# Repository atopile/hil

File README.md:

# Hardware Test 🧪 for Happy Engineers, PMs and CTOs

Hardware-in-the-Loop, or HiL (sometimes HitL), is a way to continuously validate your hardware and firmware together. By connecting actual hardware to virtual test scenarios, HiL enables thorough testing of embedded systems, control units, and firmware under realistic conditions without the risks and costs of full physical testing.

HiL testing catches integration issues early, accelerates development cycles, and ensures robust system performance before deployment. Typically the domain of the most sophisticated automotive and aerospace companies, this HiL suite is now for all 🚀.

## Usage

If you haven't already, get [atopile](https://docs.atopile.io/dev/quickstart/) and run through the quickstart and tutorial.

This suite is intended to be used as a dependency on your project. So, create a new project (`ato create project`) and add this suite as a dependency (`ato install https://github.com/atopile/hil`)

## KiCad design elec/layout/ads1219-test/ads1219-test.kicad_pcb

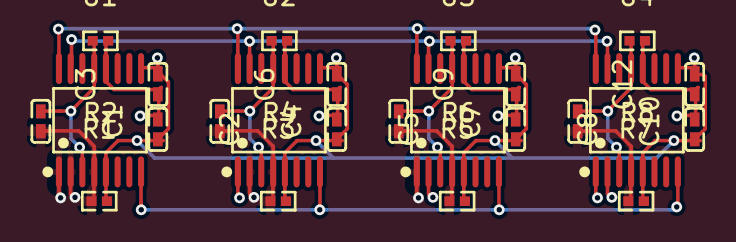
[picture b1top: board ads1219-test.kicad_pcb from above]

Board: 2 copper layers, 24 parts (0 on the bottom side), 14 nets.

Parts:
C1, C2, C3, C4, C5, C6, C7, C8, C9, C10, C11, C12: 1µF ±10% 25V X5R; C0402-b3ef17
R1, R2, R3, R4, R5, R6, R7, R8: 0Ω 62.5mW; R0402-56259e
U1, U2, U3, U4: TSSOP-16_L5.0-W4.4-P0.65-LS6.4-BL-4f6acc

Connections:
REFN: U1.8, U2.8, U3.8, U4.8
SCL: U1.16, U2.16, U3.16, U4.16
SDA: U1.15, U2.15, U3.15, U4.15
adcs[0]-AVDD: C2.1, C3.1, R2.1, U1.12
adcs[0]-gnd: C2.2, C3.2, R1.2, U1.5
adcs[1]-AVDD: C5.1, C6.1, R4.1, U2.12
adcs[1]-gnd: C5.2, C6.2, R3.2, U2.5
adcs[2]-AVDD: C8.1, C9.1, R6.1, U3.12
adcs[2]-gnd: C8.2, C9.2, R5.2, U3.5
adcs[3]-AVDD: C11.1, C12.1, R8.1, U4.12
adcs[3]-gnd: C11.2, C12.2, R7.2, U4.5
gnd: U1.9, U2.9, U3.9, U4.9
gnd-1: C1.2, C4.2, C7.2, C10.2, R1.1, R3.1, R5.1, R7.1, U1.1, U1.2, U1.4, U2.2, U2.4, U3.1, U3.4, U4.4
hv: C1.1, C4.1, C7.1, C10.1, R2.2, R4.2, R6.2, R8.2, U1.3, U1.13, U2.1, U2.3, U2.13, U3.2, U3.3, U3.13, U4.1, U4.2, U4.3, U4.13

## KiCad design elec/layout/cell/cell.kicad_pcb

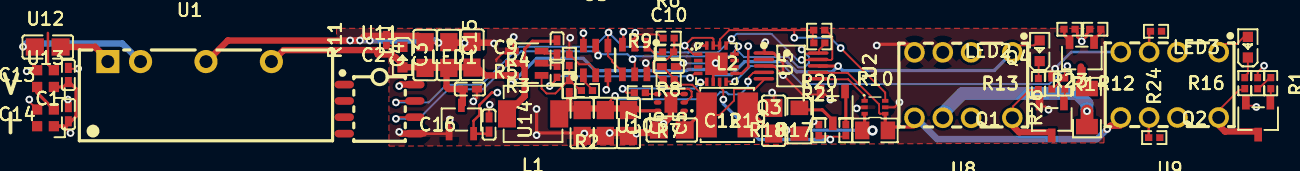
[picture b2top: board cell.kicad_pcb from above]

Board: 4 copper layers, 64 parts (0 on the bottom side), 43 nets.

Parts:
C1: 2.2µF ±10% 25V X7R; C0805-3b2e55
C2, C3, C4, C5, C6, C7, C11, C12: 10µF ±10% 25V X5R; C0805-3b2e55
C9, C13, C14: 100nF ±10% 16V X7R; C0402-b3ef17
C10, C15, C16: 1µF ±10% 25V X5R; C0402-b3ef17
L1: IND-SMD_L4.4-W4.2-3ea78a
L2: IND-SMD_L4.0-W4.0-81e2fd
LED1, LED2, LED3: LED0603-RD-c81ffb
Q1, Q2, Q3, Q4: SOT-23-3_L2.9-W1.6-P1.90-LS2.8-BR-186170
R1, R11, R14: 2kΩ ±1% 62.5mW; R0402-56259e
R2: 24kΩ ±1% 62.5mW; R0402-56259e
R3: 37.4kΩ ±1% 62.5mW; R0402-56259e
R4, R5, R8, R9, R12, R15, R18, R20, R21, R23, R24, R25: 10kΩ ±1% 62.5mW; R0402-56259e
R6: 43kΩ ±1% 62.5mW; R0402-56259e
R7: 60.4kΩ ±1% 62.5mW; R0402-56259e
R10: 100mΩ ±1% 125mW; R0805-c79e8b
R13, R16, R17, R22: 1kΩ ±1% 62.5mW; R0402-56259e
R19: 100Ω ±1% 125mW; R0805-c79e8b
R26: 100Ω ±1% 250mW; R1206-bdb864
U1: PWRM-TH_BXXXXS-2WR3-d8b2fb
U2: MSOP-10_L3.0-W3.0-P0.50-LS5.0-BL-752175
U3, U4, U10: SOT-23-6_L2.9-W1.6-P0.95-LS2.8-BL
U5: QFN-16_L3.0-W3.0-P0.50-BL-EP1.7-3a4c56
U6: WSON-6_L2.0-W2.0-P0.65-TL-EP
U7: SOT-563_L1.6-W1.2-P0.50-LS1.6-TL
U8, U9: RELAY-TH_HFDXXX-689a1e
U11: SOIC-8_L4.9-W3.9-P1.27-LS6.0-TL-e13595
U12, U13: LED-SMD_4P-L2.0-W2.0-BR-57a8d0
U14: SOT-23-3_L3.0-W1.7-P0.95-LS2.9-BR-9c7906

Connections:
3V3: C16.1, R20.2, R21.2, U3.3, U3.6, U5.1, U5.14, U5.15, U7.6, U10.3, U11.8, U14.2
3V3_GND: C2.2, C3.2, C4.2, C5.2, C6.2, C7.2, C10.2, C11.2, C12.2, C15.2, C16.2, Q1.2, Q3.2, Q4.2, R4.2, R8.2, R11.2, R13.2, R18.2, R23.2, U1.4, U2.1, U2.3, U3.2, U4.1, U5.6, U5.16, U5.17, U6.3, U6.7, U7.2, U7.5, U8.3, U8.4, U9.4, U10.2, U10.6, U11.5, U14.1
5V: C2.1, C3.1, C4.1, C15.1, LED1.2, LED2.2, U1.6, U2.8, U4.3, U8.1, U14.3
FB: R6.2, R7.2, R8.1, U6.2
SCL: R21.1, U2.10, U3.5, U5.12, U10.5, U11.6
SDA: R20.1, U2.9, U3.4, U5.13, U10.4, U11.7
SW: C9.2, L1.1, U4.2
VBST: C9.1, U4.6
VFB: R2.2, R3.2, R4.1, U4.4
buck-EN: R5.2, U4.5
buck-VOUT: R2.1, U3.1
dmm_relay-gate: Q2.1, R15.2
dmm_relay-gnd: Q2.3, R1.2, U9.8
dmm_relay.indicator_led-cathode: LED3.1, R1.1
external_load-gate: Q4.1, R22.2
gnd: R25.1, U9.3
gnd-2: Q4.3, R26.2
gnd-3: C13.2, C14.2, Q2.2, R16.2, U12.3, U13.3
gnd-4: C1.2, U1.2
gnd-5: Q3.3, R19.2
hv: C1.1, U1.1
hv-1: C10.1, C11.1, L2.1, R7.1, U2.5, U6.1
hv-2: C5.1, C6.1, C7.1, L1.2, R3.1, U2.4, U6.6
hv-3: C12.1, L2.2, R10.1, R19.1, U7.3
hv-5: R24.1, U9.6
hv-6: R26.1, U8.6
hv-7: R10.2, U2.7, U7.4, U8.5, U9.5
hv-8: C13.1, C14.1, LED3.2, U9.1, U12.1, U13.1
isolated_converter.led-cathode: LED1.1, R11.1
ldo-EN: R9.2, U6.4
ldo-VOUT: R6.1, U10.1
line: R5.1, U5.4
line-1: U12.4, U13.2
line-2: R17.1, R18.1, U5.7
line-3: R15.1, R16.1
line-4: R12.1, R13.1, U5.8
line-5: U2.6, U7.1
line-6: R9.1, U5.5
line-7: R22.1, R23.1, U5.9
load_switch-gate: Q3.1, R17.2
output_relay-gate: Q1.1, R12.2
output_relay-gnd: Q1.3, R14.2, U8.8
output_relay.indicator_led-cathode: LED2.1, R14.1

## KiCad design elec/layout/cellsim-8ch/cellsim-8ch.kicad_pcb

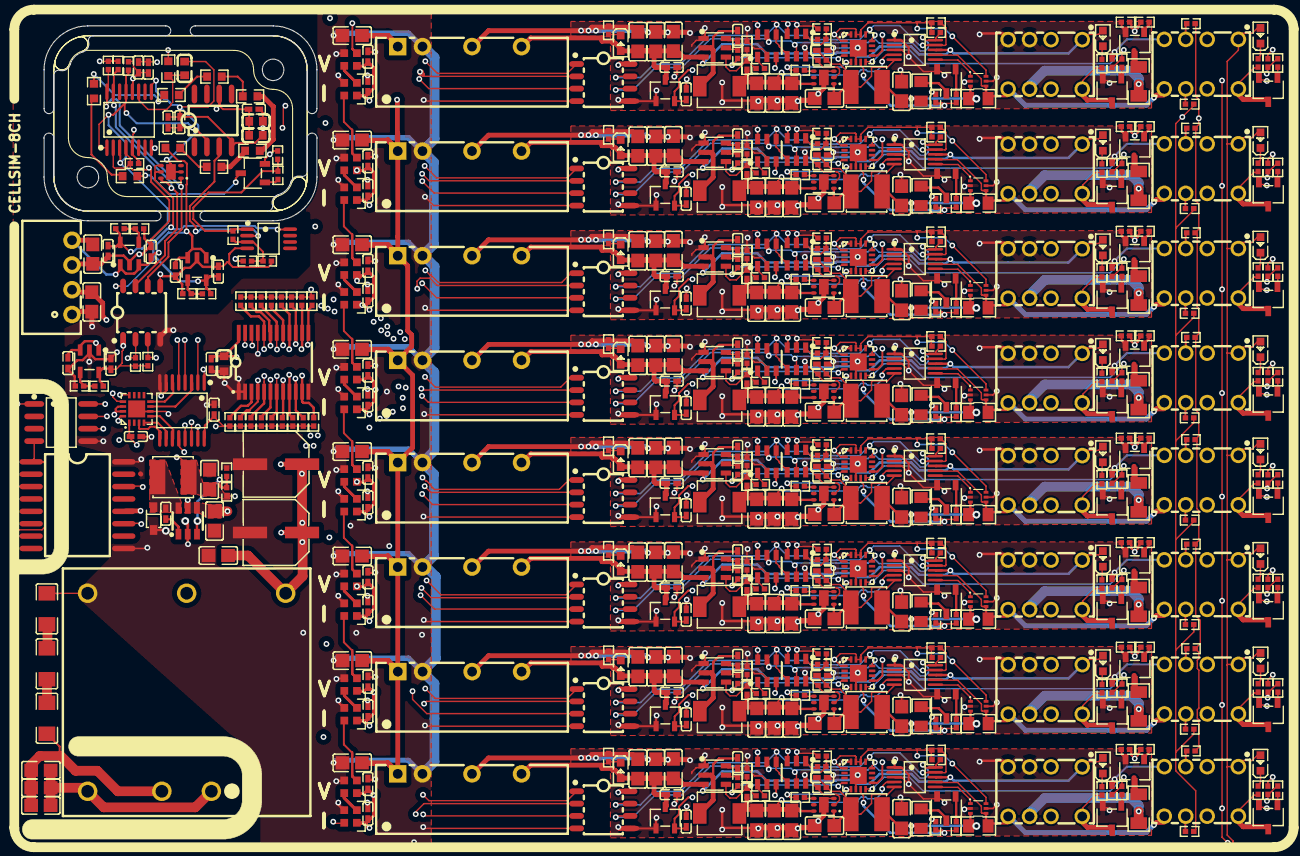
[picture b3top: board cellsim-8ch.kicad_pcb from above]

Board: 4 copper layers, 608 parts (0 on the bottom side), 377 nets.

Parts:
C1, C8, C16, C17, C24, C32, C33, C40, C48, C49, C56, C64, C65, C72, C80, C81, C88, C96, C97, C104, C112, C113, C120, C128, C129, C131: 100nF ±10% 16V X7R; C0402-b3ef17
C2, C3, C4, C5, C6, C7, C9, C10, C14, C18, C19, C20, C21, C22, C23, C25, C26, C30, C34, C35, C36, C37, C38, C39, C41, C42, C46, C50, C51, C52, C53, C54, C55, C57, C58, C62, C66, C67, C68, C69, C70, C71, C73, C74, C78, C82, C83, C84, C85, C86, C87, C89, C90, C94, C98, C99, C100, C101, C105, C106, C110, C121, C122, C126, C135: 10µF ±10% 25V X5R; C0805-3b2e55
C11, C12, C15, C27, C28, C31, C43, C44, C47, C59, C60, C63, C75, C76, C79, C91, C92, C95, C102, C103, C107, C108, C111, C114, C123, C124, C127, C130, C136, C137, C150, C151, C154, C155, C156, C157: 1µF ±10% 25V X5R; C0402-b3ef17
C13, C29, C45, C61, C77, C93, C109, C125: 2.2µF ±10% 25V X7R; C0805-3b2e55
C132: 2.2µF ±10% 16V X5R; C0603-bd72f6
C133: 470nF ±20% 16V X5R; C0402-b3ef17
C134: 4.7µF ±10% 25V X5R; C0805-3b2e55
C138, C139: 10µF ±10% 50V X5R; C0805-3b2e55
C140, C141: 1µF ±10% 50V X7R; C0805-3b2e55
C142, C143: 100µF ±20%; CAP-SMD_BD6.3-L6.6-W6.6-FD-3e301d
C144, C145, C146: 2.2nF ±10% 1kV X7R; C1206-f0a137
C152, C153: 10µF ±10% 10V X5R; C0603-bd72f6
C158, C159: 2.2µF ±10% 50V X5R; C0805-3b2e55
C160: 100nF ±10% 50V X7R; C0603-bd72f6
D1, D2, D3, D4, D5, D6, D7, D8, D9, D10, D11, D12, D13, D14, D15, D16, D17, D18, D19, D20, D21, D22, D23, D24: LED0603-RD-c81ffb
ISO1: SOIC-8_L4.9-W3.9-P1.27-LS6.0-BL-6ccfeb
L1, L3, L5, L7, L9, L11, L13, L15: IND-SMD_L4.4-W4.2-3ea78a
L2, L4, L6, L8, L10, L12, L14, L16: IND-SMD_L4.0-W4.0-81e2fd
Q1, Q2, Q3, Q4, Q5, Q6, Q7, Q8, Q9, Q10, Q11, Q12, Q13, Q14, Q15, Q16, Q17, Q18, Q19, Q20, Q21, Q22, Q23, Q24, Q25, Q26, Q27, Q28, Q29, Q30, Q31, Q32, Q33: SOT-23-3_L2.9-W1.6-P1.90-LS2.8-BR-186170
R1, R2, R6, R7, R8, R12, R14, R15, R17, R18, R23, R24, R27, R28, R32, R33, R34, R38, R40, R41, R43, R44, R49, R50, R53, R54, R58, R59, R60, R64, R66, R67, R69, R70, R75, R76, R79, R80, R84, R85, R86, R90, R92, R93, R95, R96, R101, R102, R105, R106, R110, R111, R112, R116, R118, R119, R121, R122, R127, R128, R131, R132, R136, R137, R138, R142, R144, R145, R147, R148, R153, R154, R157, R158, R162, R163, R164, R168, R170, R171, R173, R174, R179, R180, R183, R184, R188, R189, R190, R194, R196, R197, R199, R200, R205, R206, R209, R210, R211, R212, R213, R214, R215, R216, R217, R218, R219, R220, R221, R222, R223, R224, R225, R226, R227, R228, R231, R233, R247, R249: 10kΩ ±1% 62.5mW; R0402-56259e
R3, R29, R55, R81, R107, R133, R159, R185: 24kΩ ±1% 62.5mW; R0402-56259e
R4, R30, R56, R82, R108, R134, R160, R186: 37.4kΩ ±1% 62.5mW; R0402-56259e
R5, R31, R57, R83, R109, R135, R161, R187: 100mΩ ±1% 125mW; R0805-c79e8b
R9, R11, R22, R25, R35, R37, R48, R51, R61, R63, R74, R77, R87, R89, R100, R103, R113, R115, R126, R129, R139, R141, R152, R155, R165, R167, R178, R181, R191, R193, R204, R207, R243, R244: 1kΩ ±1% 62.5mW; R0402-56259e
R10, R16, R26, R36, R42, R52, R62, R68, R78, R88, R94, R104, R114, R120, R130, R140, R146, R156, R166, R172, R182, R192, R198, R208: 2kΩ ±1% 62.5mW; R0402-56259e
R13, R39, R65, R91, R117, R143, R169, R195: 100Ω ±1% 250mW; R1206-bdb864
R19, R45, R71, R97, R123, R149, R175, R201: 43kΩ ±1% 62.5mW; R0402-56259e
R20, R46, R72, R98, R124, R150, R176, R202: 60.4kΩ ±1% 62.5mW; R0402-56259e
R21, R47, R73, R99, R125, R151, R177, R203: 100Ω ±1% 125mW; R0805-c79e8b
R229: 8.2kΩ ±1% 62.5mW; R0402-56259e
R230: 47kΩ ±1% 62.5mW; R0402-56259e
R232, R250: 18kΩ ±1% 62.5mW; R0402-56259e
R234: 1MΩ ±1% 62.5mW; R0402-56259e
R235, R236, R237, R238, R239, R240, R241, R242: 15Ω ±1% 100mW; R0603-ebcab9
R245: 12kΩ ±1% 62.5mW; R0402-56259e
R246: 88.7kΩ ±0% 62.5mW; R0402-56259e
R248: 36kΩ ±1% 62.5mW; R0402-56259e
R251: 10kΩ ±1% 100mW; R0603-ebcab9
U1, U15, U29, U43, U57, U71, U85, U99: MSOP-10_L3.0-W3.0-P0.50-LS5.0-BL-752175
U2, U3, U11, U16, U17, U25, U30, U31, U39, U44, U45, U53, U58, U59, U67, U72, U73, U81, U86, U87, U95, U100, U101, U109: SOT-23-6_L2.9-W1.6-P0.95-LS2.8-BL
U4, U14, U18, U28, U32, U42, U46, U56, U60, U70, U74, U84, U88, U98, U102, U112: LED-SMD_4P-L2.0-W2.0-BR-57a8d0
U5, U19, U33, U47, U61, U75, U89, U103: SOT-563_L1.6-W1.2-P0.50-LS1.6-TL
U6, U20, U34, U48, U62, U76, U90, U104, U129: SOIC-8_L4.9-W3.9-P1.27-LS6.0-TL-e13595
U7, U13, U21, U27, U35, U41, U49, U55, U63, U69, U77, U83, U91, U97, U105, U111: RELAY-TH_HFDXXX-689a1e
U8, U22, U36, U50, U64, U78, U92, U106, U113: QFN-16_L3.0-W3.0-P0.50-BL-EP1.7-3a4c56
U9, U23, U37, U51, U65, U79, U93, U107: SOT-23-3_L3.0-W1.7-P0.95-LS2.9-BR-9c7906
U10, U24, U38, U52, U66, U80, U94, U108: PWRM-TH_BXXXXS-2WR3-d8b2fb
U12, U26, U40, U54, U68, U82, U96, U110: WSON-6_L2.0-W2.0-P0.65-TL-EP
U114, U124: TSSOP-16_L5.0-W4.4-P0.65-LS6.4-BL-4f6acc
U115: SOIC-16_L10.3-W7.4-P1.27-LS10.3-BL-0756a5
U116: TSSOP-24_L7.8-W4.4-P0.65-LS6.4-BL
U117: SOD-323_L1.8-W1.3-LS2.5-RD
U118: SOT-23-6_L2.9-W1.6-P0.95-LS2.8-BR
U119: 10µH ±20%; IND-SMD_L4.0-W4.0
U120, U127, U130: SOT-23-5_L3.0-W1.7-P0.95-LS2.8-BL
U121: PWRM-TH_TDPOWER_TDK20-XXSXXWH-ae86e0
U122, U123: 0Ω 62.5mW; R0402-56259e
U125: VSSOP-8_L3.0-W3.0-P0.65-LS4.9-BL-beff67
U126: SOIC-8_L5.0-W4.0-P1.27-LS6.0-BL-294f77
U128: WSON-6_L2.0-W2.0-P0.65-TL-EP-c93430
U131: PWRM-TH_BXXXXS-1WR3-00ecee

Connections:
3V3: C28.1, R40.2, R41.2, U16.3, U16.6, U19.6, U20.8, U22.1, U22.14, U22.15, U23.2, U25.3
3V3-1: C60.1, R92.2, R93.2, U44.3, U44.6, U47.6, U48.8, U50.1, U50.14, U50.15, U51.2, U53.3
3V3-2: C124.1, R196.2, R197.2, U100.3, U100.6, U103.6, U104.8, U106.1, U106.14, U106.15, U107.2, U109.3
3V3-3: C108.1, R170.2, R171.2, U86.3, U86.6, U89.6, U90.8, U92.1, U92.14, U92.15, U93.2, U95.3
3V3-4: C76.1, R118.2, R119.2, U58.3, U58.6, U61.6, U62.8, U64.1, U64.14, U64.15, U65.2, U67.3
3V3-5: C12.1, R14.2, R15.2, U2.3, U2.6, U5.6, U6.8, U8.1, U8.14, U8.15, U9.2, U11.3
3V3-6: C92.1, R144.2, R145.2, U72.3, U72.6, U75.6, U76.8, U78.1, U78.14, U78.15, U79.2, U81.3
3V3-7: C44.1, R66.2, R67.2, U30.3, U30.6, U33.6, U34.8, U36.1, U36.14, U36.15, U37.2, U39.3
5V: C22.1, C23.1, C43.1, C46.1, D8.2, D9.2, U29.8, U31.3, U37.3, U38.6, U41.1
5V-1: C37.1, C38.1, C59.1, C62.1, D11.2, D12.2, U43.8, U45.3, U51.3, U52.6, U55.1
5V-2: C67.1, C68.1, C91.1, C94.1, D17.2, D18.2, U71.8, U73.3, U79.3, U80.6, U83.1
5V-3: C87.1, C98.1, C123.1, C126.1, D23.2, D24.2, U99.8, U101.3, U107.3, U108.6, U111.1
5V-4: C7.1, C18.1, C27.1, C30.1, D5.2, D6.2, U15.8, U17.3, U23.3, U24.6, U27.1
5V-5: C2.1, C3.1, C11.1, C14.1, D2.2, D3.2, U1.8, U3.3, U9.3, U10.6, U13.1
5V-6: C52.1, C53.1, C75.1, C78.1, D14.2, D15.2, U57.8, U59.3, U65.3, U66.6, U69.1
5V-7: C82.1, C83.1, C107.1, C110.1, D20.2, D21.2, U85.8, U87.3, U93.3, U94.6, U97.1
A: U113.7, U114.3
AVDD: C103.1, C114.1, U123.1, U124.12
CB: C133.1, U118.1
Eh: U113.8, U114.6
IN1plus: R234.2, R245.1, R246.2, U125.3
OUT1: R234.1, R243.1, R244.1, U125.1
RESET_: R228.1, U116.3
S0: U113.5, U114.11
S1: U113.4, U114.10
S2: U113.3, U114.9
SCL: R144.1, U71.10, U72.5, U76.6, U78.12, U81.5
SCL-1: R170.1, U85.10, U86.5, U90.6, U92.12, U95.5
SCL-2: R211.1, U124.16, U128.1, U129.6
SCL-3: R66.1, U29.10, U30.5, U34.6, U36.12, U39.5
SCL-4: R14.1, U1.10, U2.5, U6.6, U8.12, U11.5
SCL-5: R92.1, U43.10, U44.5, U48.6, U50.12, U53.5
SCL-6: R40.1, U15.10, U16.5, U20.6, U22.12, U25.5
SCL-7: R118.1, U57.10, U58.5, U62.6, U64.12, U67.5
SCL-8: R209.1, U113.12, U115.11, U116.22, U129.3
SCL-9: R196.1, U99.10, U100.5, U104.6, U106.12, U109.5
SDA: R145.1, U71.9, U72.4, U76.7, U78.13, U81.4
SDA-1: R197.1, U99.9, U100.4, U104.7, U106.13, U109.4
SDA-2: R93.1, U43.9, U44.4, U48.7, U50.13, U53.4
SDA-3: R41.1, U15.9, U16.4, U20.7, U22.13, U25.4
SDA-4: R210.1, U113.13, U115.12, U116.23, U129.2
SDA-5: R119.1, U57.9, U58.4, U62.7, U64.13, U67.4
SDA-6: R15.1, U1.9, U2.4, U6.7, U8.13, U11.4
SDA-7: R171.1, U85.9, U86.4, U90.7, U92.13, U95.4
SDA-8: R67.1, U29.9, U30.4, U34.7, U36.13, U39.4
SDA-9: R233.1, U124.15, U128.6, U129.7
TEMP: U125.2, U126.3
buck_5v-FB: R229.1, R230.2, U118.3
buck_5v-cathode: C133.2, U117.1, U118.6, U119.1
cell1-gnd: Q3.3, R21.2
cell1-gnd-1: Q2.3, R13.2
cell1-gnd-2: R6.1, U7.3
cell1-hv: R13.1, U13.6
cell1-hv-1: C4.1, C5.1, C6.1, L1.2, R4.1, U1.4, U12.6
cell1-hv-2: R7.1, U7.6
cell1-hv-3: C9.1, C15.1, L2.1, R20.1, U1.5, U12.1
cell1-hv-4: R5.2, U1.7, U5.4, U7.5, U13.5
cell1-line: R22.1, R23.1, U8.7
cell1-line-1: R17.1, U8.5
cell1-line-2: R11.1, R12.1, U8.9
cell1-line-3: U4.2, U14.4
cell1-line-4: R1.1, U8.4
cell1-line-5: U1.6, U5.1
cell1-line-6: R24.1, R25.1, U8.8
cell1.buck-EN: R1.2, U3.5
cell1.buck-SW: C1.2, L1.1, U3.2
cell1.buck-VBST: C1.1, U3.6
cell1.buck-VFB: R2.1, R3.2, R4.2, U3.4
cell1.buck-VOUT: R3.1, U2.1
cell1.dmm_relay-gate: Q1.1, R8.2
cell1.dmm_relay-gnd: Q1.3, R10.2, U7.8
cell1.dmm_relay.indicator_led-cathode: D1.1, R10.1
cell1.external_load-gate: Q2.1, R11.2
cell1.isolated_converter.led-cathode: D2.1, R16.1
cell1.ldo-EN: R17.2, U12.4
cell1.ldo-FB: R18.1, R19.2, R20.2, U12.2
cell1.ldo-VOUT: R19.1, U11.1
cell1.load_switch-gate: Q3.1, R22.2
cell1.output_relay-gate: Q4.1, R24.2
cell1.output_relay-gnd: Q4.3, R26.2, U13.8
cell1.output_relay.indicator_led-cathode: D3.1, R26.1
cell2-gnd: Q7.3, R47.2
cell2-gnd-1: Q6.3, R39.2
cell2-gnd-2: R32.1, U21.3
cell2-hv: R39.1, U27.6
cell2-hv-1: R31.2, U15.7, U19.4, U21.5, U27.5
cell2-hv-2: C25.1, C31.1, L4.1, R46.1, U15.5, U26.1
cell2-hv-3: C19.1, C20.1, C21.1, L3.2, R30.1, U15.4, U26.6
cell2-hv-4: R33.1, U21.6
cell2-line: R27.1, U22.4
cell2-line-1: R43.1, U22.5
cell2-line-2: U15.6, U19.1
cell2-line-3: U18.2, U28.4
cell2-line-4: R48.1, R49.1, U22.7
cell2-line-5: R50.1, R51.1, U22.8
cell2-line-6: R37.1, R38.1, U22.9
cell2.buck-EN: R27.2, U17.5
cell2.buck-SW: C17.2, L3.1, U17.2
cell2.buck-VBST: C17.1, U17.6
cell2.buck-VFB: R28.1, R29.2, R30.2, U17.4
cell2.buck-VOUT: R29.1, U16.1
cell2.dmm_relay-gate: Q5.1, R34.2
cell2.dmm_relay-gnd: Q5.3, R36.2, U21.8
cell2.dmm_relay.indicator_led-cathode: D4.1, R36.1
cell2.external_load-gate: Q6.1, R37.2
cell2.isolated_converter.led-cathode: D5.1, R42.1
cell2.ldo-EN: R43.2, U26.4
cell2.ldo-FB: R44.1, R45.2, R46.2, U26.2
cell2.ldo-VOUT: R45.1, U25.1
cell2.load_switch-gate: Q7.1, R48.2
cell2.output_relay-gate: Q8.1, R50.2
cell2.output_relay-gnd: Q8.3, R52.2, U27.8
cell2.output_relay.indicator_led-cathode: D6.1, R52.1
cell3-gnd: Q11.3, R73.2
cell3-gnd-1: Q10.3, R65.2
cell3-gnd-2: R58.1, U35.3
cell3-hv: R59.1, U35.6
cell3-hv-1: R57.2, U29.7, U33.4, U35.5, U41.5
cell3-hv-2: C34.1, C35.1, C36.1, L5.2, R56.1, U29.4, U40.6
cell3-hv-3: C41.1, C47.1, L6.1, R72.1, U29.5, U40.1
cell3-hv-4: R65.1, U41.6
cell3-line: U29.6, U33.1
cell3-line-1: R74.1, R75.1, U36.7
cell3-line-2: R63.1, R64.1, U36.9
cell3-line-3: R69.1, U36.5
cell3-line-4: R53.1, U36.4
cell3-line-5: U32.2, U42.4
cell3-line-6: R76.1, R77.1, U36.8
cell3.buck-EN: R53.2, U31.5
cell3.buck-SW: C33.2, L5.1, U31.2
cell3.buck-VBST: C33.1, U31.6
cell3.buck-VFB: R54.1, R55.2, R56.2, U31.4
cell3.buck-VOUT: R55.1, U30.1
cell3.dmm_relay-gate: Q9.1, R60.2
cell3.dmm_relay-gnd: Q9.3, R62.2, U35.8
cell3.dmm_relay.indicator_led-cathode: D7.1, R62.1
cell3.external_load-gate: Q10.1, R63.2
cell3.isolated_converter.led-cathode: D8.1, R68.1
cell3.ldo-EN: R69.2, U40.4
cell3.ldo-FB: R70.1, R71.2, R72.2, U40.2
cell3.ldo-VOUT: R71.1, U39.1
cell3.load_switch-gate: Q11.1, R74.2
cell3.output_relay-gate: Q12.1, R76.2
cell3.output_relay-gnd: Q12.3, R78.2, U41.8
cell3.output_relay.indicator_led-cathode: D9.1, R78.1
cell4-gnd: Q14.3, R91.2
cell4-gnd-1: R84.1, U49.3
cell4-gnd-2: Q15.3, R99.2
cell4-hv: R83.2, U43.7, U47.4, U49.5, U55.5
cell4-hv-1: C39.1, C50.1, C51.1, L7.2, R82.1, U43.4, U54.6
cell4-hv-2: C57.1, C63.1, L8.1, R98.1, U43.5, U54.1
cell4-hv-3: R91.1, U55.6
cell4-hv-4: R85.1, U49.6
cell4-line: R102.1, R103.1, U50.8
cell4-line-1: R89.1, R90.1, U50.9
cell4-line-2: R100.1, R101.1, U50.7
cell4-line-3: U43.6, U47.1
cell4-line-4: R95.1, U50.5
cell4-line-5: R79.1, U50.4
cell4-line-6: U46.2, U56.4
cell4.buck-EN: R79.2, U45.5
cell4.buck-SW: C49.2, L7.1, U45.2
cell4.buck-VBST: C49.1, U45.6
cell4.buck-VFB: R80.1, R81.2, R82.2, U45.4
cell4.buck-VOUT: R81.1, U44.1
cell4.dmm_relay-gate: Q13.1, R86.2
cell4.dmm_relay-gnd: Q13.3, R88.2, U49.8
cell4.dmm_relay.indicator_led-cathode: D10.1, R88.1
cell4.external_load-gate: Q14.1, R89.2
cell4.isolated_converter.led-cathode: D11.1, R94.1
cell4.ldo-EN: R95.2, U54.4
cell4.ldo-FB: R96.1, R97.2, R98.2, U54.2
cell4.ldo-VOUT: R97.1, U53.1
cell4.load_switch-gate: Q15.1, R100.2
cell4.output_relay-gate: Q16.1, R102.2
cell4.output_relay-gnd: Q16.3, R104.2, U55.8
cell4.output_relay.indicator_led-cathode: D12.1, R104.1
cell5-gnd: R110.1, U63.3
cell5-gnd-1: Q19.3, R125.2
cell5-gnd-2: Q18.3, R117.2
cell5-hv: C73.1, C79.1, L10.1, R124.1, U57.5, U68.1
cell5-hv-1: R117.1, U69.6
cell5-hv-2: R109.2, U57.7, U61.4, U63.5, U69.5
cell5-hv-3: R111.1, U63.6
cell5-hv-4: C54.1, C55.1, C66.1, L9.2, R108.1, U57.4, U68.6
cell5-line: R128.1, R129.1, U64.8
cell5-line-1: R126.1, R127.1, U64.7
cell5-line-2: R121.1, U64.5
cell5-line-3: R115.1, R116.1, U64.9
cell5-line-4: U57.6, U61.1
cell5-line-5: U60.2, U70.4
cell5-line-6: R105.1, U64.4
cell5.buck-EN: R105.2, U59.5
cell5.buck-SW: C65.2, L9.1, U59.2
cell5.buck-VBST: C65.1, U59.6
cell5.buck-VFB: R106.1, R107.2, R108.2, U59.4
cell5.buck-VOUT: R107.1, U58.1
cell5.dmm_relay-gate: Q17.1, R112.2
cell5.dmm_relay-gnd: Q17.3, R114.2, U63.8
cell5.dmm_relay.indicator_led-cathode: D13.1, R114.1
cell5.external_load-gate: Q18.1, R115.2
cell5.isolated_converter.led-cathode: D14.1, R120.1
cell5.ldo-EN: R121.2, U68.4
cell5.ldo-FB: R122.1, R123.2, R124.2, U68.2
cell5.ldo-VOUT: R123.1, U67.1
cell5.load_switch-gate: Q19.1, R126.2
cell5.output_relay-gate: Q20.1, R128.2
cell5.output_relay-gnd: Q20.3, R130.2, U69.8
cell5.output_relay.indicator_led-cathode: D15.1, R130.1
cell6-gnd: Q23.3, R151.2
cell6-gnd-1: Q22.3, R143.2
cell6-gnd-2: R136.1, U77.3
cell6-hv: C89.1, C95.1, L12.1, R150.1, U71.5, U82.1
cell6-hv-1: R135.2, U71.7, U75.4, U77.5, U83.5
cell6-hv-2: R137.1, U77.6
cell6-hv-3: R143.1, U83.6
cell6-hv-4: C69.1, C70.1, C71.1, L11.2, R134.1, U71.4, U82.6
cell6-line: R154.1, R155.1, U78.8
cell6-line-1: U71.6, U75.1
cell6-line-2: R147.1, U78.5
cell6-line-3: R152.1, R153.1, U78.7
cell6-line-4: R131.1, U78.4
cell6-line-5: R141.1, R142.1, U78.9
cell6-line-6: U74.2, U84.4
cell6.buck-EN: R131.2, U73.5
cell6.buck-SW: C81.2, L11.1, U73.2
cell6.buck-VBST: C81.1, U73.6
cell6.buck-VFB: R132.1, R133.2, R134.2, U73.4
cell6.buck-VOUT: R133.1, U72.1
cell6.dmm_relay-gate: Q21.1, R138.2
cell6.dmm_relay-gnd: Q21.3, R140.2, U77.8
cell6.dmm_relay.indicator_led-cathode: D16.1, R140.1
cell6.external_load-gate: Q22.1, R141.2
cell6.isolated_converter.led-cathode: D17.1, R146.1
cell6.ldo-EN: R147.2, U82.4
cell6.ldo-FB: R148.1, R149.2, R150.2, U82.2
cell6.ldo-VOUT: R149.1, U81.1
cell6.load_switch-gate: Q23.1, R152.2
cell6.output_relay-gate: Q24.1, R154.2
cell6.output_relay-gnd: Q24.3, R156.2, U83.8
cell6.output_relay.indicator_led-cathode: D18.1, R156.1
cell7-gnd: Q26.3, R169.2
cell7-gnd-1: R162.1, U91.3
cell7-gnd-2: Q27.3, R177.2
cell7-hv: R169.1, U97.6
cell7-hv-1: R163.1, U91.6
cell7-hv-2: C105.1, C111.1, L14.1, R176.1, U85.5, U96.1
cell7-hv-3: C84.1, C85.1, C86.1, L13.2, R160.1, U85.4, U96.6
cell7-hv-4: R161.2, U85.7, U89.4, U91.5, U97.5
cell7-line: R167.1, R168.1, U92.9
cell7-line-1: R180.1, R181.1, U92.8
cell7-line-2: R173.1, U92.5
cell7-line-3: R157.1, U92.4
cell7-line-4: R178.1, R179.1, U92.7
cell7-line-5: U85.6, U89.1
cell7-line-6: U88.2, U98.4
cell7.buck-EN: R157.2, U87.5
cell7.buck-SW: C97.2, L13.1, U87.2
cell7.buck-VBST: C97.1, U87.6
cell7.buck-VFB: R158.1, R159.2, R160.2, U87.4
cell7.buck-VOUT: R159.1, U86.1
cell7.dmm_relay-gate: Q25.1, R164.2
cell7.dmm_relay-gnd: Q25.3, R166.2, U91.8
cell7.dmm_relay.indicator_led-cathode: D19.1, R166.1
cell7.external_load-gate: Q26.1, R167.2
cell7.isolated_converter.led-cathode: D20.1, R172.1
cell7.ldo-EN: R173.2, U96.4
cell7.ldo-FB: R174.1, R175.2, R176.2, U96.2
cell7.ldo-VOUT: R175.1, U95.1
cell7.load_switch-gate: Q27.1, R178.2
cell7.output_relay-gate: Q28.1, R180.2
cell7.output_relay-gnd: Q28.3, R182.2, U97.8
cell7.output_relay.indicator_led-cathode: D21.1, R182.1
cell8-gnd: R188.1, U105.3
cell8-gnd-1: Q30.3, R195.2
cell8-gnd-2: Q31.3, R203.2
cell8-hv: R195.1, U111.6
cell8-hv-1: C121.1, C127.1, L16.1, R202.1, U99.5, U110.1
cell8-hv-2: C99.1, C100.1, C101.1, L15.2, R186.1, U99.4, U110.6
cell8-hv-3: R187.2, U99.7, U103.4, U105.5, U111.5
cell8-hv-4: R189.1, U105.6
cell8-line: U99.6, U103.1
cell8-line-1: R199.1, U106.5
cell8-line-2: R204.1, R205.1, U106.7
cell8-line-3: R193.1, R194.1, U106.9
cell8-line-4: R206.1, R207.1, U106.8
cell8-line-5: R183.1, U106.4
cell8-line-6: U102.2, U112.4
cell8.buck-EN: R183.2, U101.5
cell8.buck-SW: C113.2, L15.1, U101.2
cell8.buck-VBST: C113.1, U101.6
cell8.buck-VFB: R184.1, R185.2, R186.2, U101.4
cell8.buck-VOUT: R185.1, U100.1
cell8.dmm_relay-gate: Q29.1, R190.2
cell8.dmm_relay-gnd: Q29.3, R192.2, U105.8
cell8.dmm_relay.indicator_led-cathode: D22.1, R192.1
cell8.external_load-gate: Q30.1, R193.2
cell8.isolated_converter.led-cathode: D23.1, R198.1
cell8.ldo-EN: R199.2, U110.4
cell8.ldo-FB: R200.1, R201.2, R202.2, U110.2
cell8.ldo-VOUT: R201.1, U109.1
cell8.load_switch-gate: Q31.1, R204.2
cell8.output_relay-gate: Q32.1, R206.2
cell8.output_relay-gnd: Q32.3, R208.2, U111.8
cell8.output_relay.indicator_led-cathode: D24.1, R208.1
gnd: C82.2, C83.2, C84.2, C85.2, C86.2, C90.1, C105.2, C106.2, C107.2, C108.2, C110.2, C111.2, L12.2, Q26.2, Q27.2, Q28.2, R135.1, R151.1, R158.2, R168.2, R172.2, R174.2, R179.2, R181.2, U75.3, U85.1, U85.3, U86.2, U87.1, U89.2, U89.5, U90.5, U91.4, U92.6, U92.16, U92.17, U93.1, U94.4, U95.2, U95.6, U96.3, U96.7, U97.3, U97.4
gnd-1: C87.2, C98.2, C99.2, C100.2, C101.2, C106.1, C121.2, C122.2, C123.2, C124.2, C126.2, C127.2, L14.2, Q30.2, Q31.2, Q32.2, R161.1, R177.1, R184.2, R194.2, R198.2, R200.2, R205.2, R207.2, U89.3, U99.1, U99.3, U100.2, U101.1, U103.2, U103.5, U104.5, U105.4, U106.6, U106.16, U106.17, U107.1, U108.4, U109.2, U109.6, U110.3, U110.7, U111.3, U111.4
gnd-2: C37.2, C38.2, C39.2, C42.1, C50.2, C51.2, C57.2, C58.2, C59.2, C60.2, C62.2, C63.2, L6.2, Q14.2, Q15.2, Q16.2, R57.1, R73.1, R80.2, R90.2, R94.2, R96.2, R101.2, R103.2, U33.3, U43.1, U43.3, U44.2, U45.1, U47.2, U47.5, U48.5, U49.4, U50.6, U50.16, U50.17, U51.1, U52.4, U53.2, U53.6, U54.3, U54.7, U55.3, U55.4
gnd-3: C52.2, C53.2, C54.2, C55.2, C58.1, C66.2, C73.2, C74.2, C75.2, C76.2, C78.2, C79.2, L8.2, Q18.2, Q19.2, Q20.2, R83.1, R99.1, R106.2, R116.2, R120.2, R122.2, R127.2, R129.2, U47.3, U57.1, U57.3, U58.2, U59.1, U61.2, U61.5, U62.5, U63.4, U64.6, U64.16, U64.17, U65.1, U66.4, U67.2, U67.6, U68.3, U68.7, U69.3, U69.4
gnd-4: C22.2, C23.2, C26.1, C34.2, C35.2, C36.2, C41.2, C42.2, C43.2, C44.2, C46.2, C47.2, L4.2, Q10.2, Q11.2, Q12.2, R31.1, R47.1, R54.2, R64.2, R68.2, R70.2, R75.2, R77.2, U19.3, U29.1, U29.3, U30.2, U31.1, U33.2, U33.5, U34.5, U35.4, U36.6, U36.16, U36.17, U37.1, U38.4, U39.2, U39.6, U40.3, U40.7, U41.3, U41.4
gnd-5: ISO1.4, U115.1, U115.7
gnd-6: C138.2, C139.2, C140.2, C144.1, U121.2
gnd-7: C102.2, C150.2, C151.2, C152.2, C153.2, C154.2, C155.2, C156.2, C157.2, C159.2, C160.2, Q33.2, R6.2, R32.2, R58.2, R84.2, R110.2, R136.2, R162.2, R188.2, R244.2, R245.2, R247.2, R249.2, U122.1, U124.2, U124.4, U124.9, U125.4, U126.4, U127.2, U128.2, U128.7, U129.5, U130.2, U131.3
gnd-8: C67.2, C68.2, C69.2, C70.2, C71.2, C74.1, C89.2, C90.2, C91.2, C92.2, C94.2, C95.2, L10.2, Q22.2, Q23.2, Q24.2, R109.1, R125.1, R132.2, R142.2, R146.2, R148.2, R153.2, R155.2, U61.3, U71.1, U71.3, U72.2, U73.1, U75.2, U75.5, U76.5, U77.4, U78.6, U78.16, U78.17, U79.1, U80.4, U81.2, U81.6, U82.3, U82.7, U83.3, U83.4
gnd-9: C103.2, C114.2, U122.2, U124.5
gnd-10: C8.2, C13.2, C16.2, C24.2, C29.2, C32.2, C40.2, C45.2, C48.2, C56.2, C61.2, C64.2, C72.2, C77.2, C80.2, C88.2, C93.2, C96.2, C104.2, C109.2, C112.2, C120.2, C125.2, C128.2, C129.2, C130.2, C131.2, C132.2, C134.2, C135.2, C136.2, C137.2, C141.2, C142.2, C143.2, C146.2, C158.2, ISO1.5, Q1.2, Q5.2, Q9.2, Q13.2, Q17.2, Q21.2, Q25.2, Q29.2, R9.2, R35.2, R61.2, R87.2, R113.2, R139.2, R165.2, R191.2, R229.2, R231.2, U4.3, U6.4, U10.2, U14.3, U18.3, U20.4, U24.2, U28.3, U32.3, U34.4, U38.2, U42.3, U46.3, U48.4, U52.2, U56.3, U60.3, U62.4, U66.2, U70.3, U74.3, U76.4, U80.2, U84.3, U88.3, U90.4, U94.2, U98.3, U102.3, U104.4, U108.2, U112.3, U113.6, U113.17, U114.7, U114.8, U115.9, U115.16, U116.1, U116.2, U116.12, U116.21, U117.2, U118.2, U120.2, U121.4, U129.4, U131.1
gnd-11: C2.2, C3.2, C4.2, C5.2, C6.2, C9.2, C10.2, C11.2, C12.2, C14.2, C15.2, Q2.2, Q3.2, Q4.2, R2.2, R12.2, R16.2, R18.2, R23.2, R25.2, U1.1, U1.3, U2.2, U3.1, U5.2, U5.5, U6.5, U7.4, U8.6, U8.16, U8.17, U9.1, U10.4, U11.2, U11.6, U12.3, U12.7, U13.3, U13.4
gnd-12: C7.2, C10.1, C18.2, C19.2, C20.2, C21.2, C25.2, C26.2, C27.2, C28.2, C30.2, C31.2, L2.2, Q6.2, Q7.2, Q8.2, R5.1, R21.1, R28.2, R38.2, R42.2, R44.2, R49.2, R51.2, U5.3, U15.1, U15.3, U16.2, U17.1, U19.2, U19.5, U20.5, U21.4, U22.6, U22.16, U22.17, U23.1, U24.4, U25.2, U25.6, U26.3, U26.7, U27.3, U27.4
hv: C8.1, C16.1, C24.1, C32.1, C40.1, C48.1, C56.1, C64.1, C72.1, C80.1, C88.1, C96.1, C104.1, C112.1, C120.1, C128.1, C135.1, C136.1, D1.2, D4.2, D7.2, D10.2, D13.2, D16.2, D19.2, D22.2, ISO1.8, R230.1, U4.1, U7.1, U14.1, U18.1, U21.1, U28.1, U32.1, U35.1, U42.1, U46.1, U49.1, U56.1, U60.1, U63.1, U70.1, U74.1, U77.1, U84.1, U88.1, U91.1, U98.1, U102.1, U105.1, U112.1, U119.2, U120.1, U120.3
hv-1: ISO1.1, U115.3
hv-2: R7.2, R33.2, R59.2, R85.2, R111.2, R137.2, R163.2, R189.2, R251.1
hv-3: C138.1, C139.1, C140.1, U121.1, U121.3
hv-4: C157.1, R211.2, R233.2, R250.1, U125.8, U128.4, U128.5, U129.8, U130.5
hv-5: C13.1, C29.1, C45.1, C61.1, C77.1, C93.1, C109.1, C125.1, C134.1, C141.1, C142.1, C143.1, C158.1, U10.1, U24.1, U38.1, U52.1, U66.1, U80.1, U94.1, U108.1, U118.4, U118.5, U121.6, U131.2
hv-6: C154.1, C156.1, C159.1, R235.1, U127.1, U127.3, U130.1, U130.3, U131.4
hv-7: C129.1, C130.1, C131.1, C132.1, C137.1, R209.2, R210.2, R212.2, R213.2, R214.2, R215.2, R216.2, R217.2, R218.2, R219.2, R220.2, R221.2, R222.2, R223.2, R224.2, R225.2, R226.2, R227.2, R228.2, R232.1, U6.1, U20.1, U34.1, U48.1, U62.1, U76.1, U90.1, U104.1, U113.1, U113.14, U113.15, U114.16, U115.14, U116.24, U120.5, U129.1
hv-8: C122.1, L16.2, R187.1, R203.1, U103.3
ldo_3v3-ADJ_NC: R231.1, R232.2, U120.4
line: R60.1, R61.1, U114.15
line-1: R86.1, R87.1, U114.12
line-2: U84.2, U88.4
line-3: R112.1, R113.1, U114.1
line-4: U42.2, U46.4
line-5: U14.2, U18.4
line-6: U56.2, U60.4
line-7: R190.1, R191.1, U114.4
line-8: ISO1.7, U112.2
line-9: R164.1, R165.1, U114.2
line-10: R138.1, R139.1, U114.5
line-11: C160.1, R251.2, U124.11
line-12: U98.2, U102.4
line-13: U28.2, U32.4
line-14: U70.2, U74.4
line-15: R34.1, R35.1, U114.14
line-16: R8.1, R9.1, U114.13
line-17: ISO1.6, U4.4
micro_vault-hv: C151.1, C152.1, C153.1, U124.8, U126.6
micro_vault-hv-1: C102.1, C150.1, C155.1, R246.1, R248.1, U123.2, U124.1, U124.3, U124.13, U126.2, U127.5
micro_vault.heater_controller-gnd: Q33.3, R242.2
micro_vault.heater_controller-net: R240.2, R241.1
micro_vault.heater_controller-net-1: R235.2, R236.1
micro_vault.heater_controller-net-2: R241.2, R242.1
micro_vault.heater_controller-net-3: R239.2, R240.1
micro_vault.heater_controller-net-4: R237.2, R238.1
micro_vault.heater_controller-net-5: R236.2, R237.1
micro_vault.heater_controller-net-6: R238.2, R239.1
micro_vault.heater_controller.load_switch-gate: Q33.1, R243.2
micro_vault.reference_regulator-ADJ_NC: R247.1, R248.2, U127.4
micro_vault_ldo_3v3-ADJ_NC: R249.1, R250.2, U130.4
regulator_24v_isolated-net: C144.2, C145.1
regulator_24v_isolated-net-1: C145.2, C146.1
scl1: R226.1, U104.3, U116.20
scl1-1: R222.1, U76.3, U116.16
scl1-2: R224.1, U90.3, U116.18
scl1-3: R220.1, U62.3, U116.14
scl1-4: R212.1, U6.3, U116.5
scl1-6: R214.1, U20.3, U116.7
scl1-7: R218.1, U48.3, U116.11
scl1-8: R216.1, U34.3, U116.9
sda1: R215.1, U20.2, U116.6
sda1-1: R227.1, U104.2, U116.19
sda1-2: R223.1, U76.2, U116.15
sda1-3: R213.1, U6.2, U116.4
sda1-5: R217.1, U34.2, U116.8
sda1-6: R219.1, U48.2, U116.10
sda1-7: R225.1, U90.2, U116.17
sda1-8: R221.1, U62.2, U116.13

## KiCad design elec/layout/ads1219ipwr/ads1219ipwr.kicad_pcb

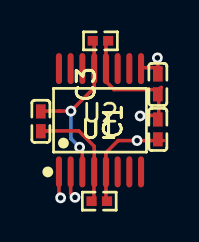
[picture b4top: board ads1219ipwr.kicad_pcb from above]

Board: 2 copper layers, 6 parts (0 on the bottom side), 4 nets.

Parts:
C1, C2, C3: 1µF ±10% 25V X5R; C0402-b3ef17
U1, U2: 0Ω 62.5mW; R0402-56259e
U3: TSSOP-16_L5.0-W4.4-P0.65-LS6.4-BL-4f6acc

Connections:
gnd: C2.2, C3.2, U1.2, U3.5, U3.9
gnd-1: C1.2, U1.1, U3.4
hv: C1.1, U2.2, U3.3, U3.13
hv-1: C2.1, C3.1, U2.1, U3.12

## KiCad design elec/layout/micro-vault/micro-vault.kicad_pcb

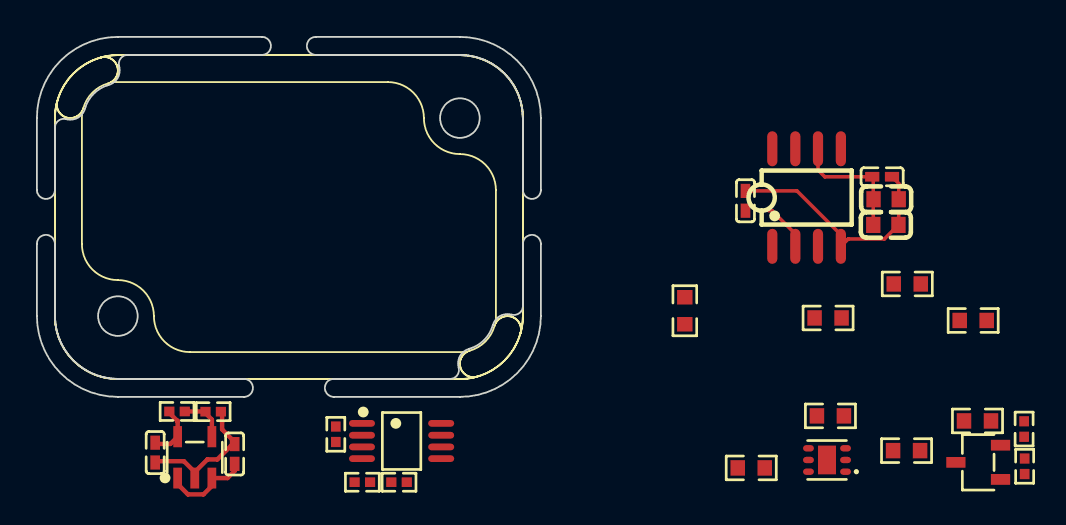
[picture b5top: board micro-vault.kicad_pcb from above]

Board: 2 copper layers, 28.0 x 20.0 mm, 26 parts (0 on the bottom side), 18 nets.

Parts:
C4, C5, C8, C9: 1µF ±10% 25V X5R; C0402-b3ef17
C6, C7: 10µF ±10% 10V X5R; C0603-bd72f6
Q1: SOT-23-3_L2.9-W1.6-P1.90-LS2.8-BR-186170
R1: 1MΩ ±1% 62.5mW; R0402-56259e
R2, R3, R4, R5, R12, R13, R14, R15: 15Ω ±1% 100mW; R0603-ebcab9
R6, R7, R10: 10kΩ ±1% 62.5mW; R0402-56259e
R8: 12kΩ ±1% 62.5mW; R0402-56259e
R9: 88.7kΩ ±0% 62.5mW; R0402-56259e
R11: 36kΩ ±1% 62.5mW; R0402-56259e
U5: VSSOP-8_L3.0-W3.0-P0.65-LS4.9-BL-beff67
U6: SOIC-8_L5.0-W4.0-P1.27-LS6.0-BL-294f77
U7: SOT-23-5_L3.0-W1.7-P0.95-LS2.8-BL
U8: WSON-6_L2.0-W2.0-P0.65-TL-EP-c93430

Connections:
ADJ_NC: R10.1, R11.2, U7.4
IN1plus: R1.2, R8.1, R9.2, U5.3
OUT1: R1.1, R6.1, R7.1, U5.1
TEMP: U5.2, U6.3
Vplus: U5.8, U8.5
gate: Q1.1, R6.2
gnd: C4.2, C5.2, C6.2, C7.2, C8.2, C9.2, Q1.2, R7.2, R8.2, R10.2, U5.4, U6.4, U7.2, U8.2, U8.4, U8.7
heater_controller-gnd: Q1.3, R15.2
heater_controller-net: R2.2, R3.1
heater_controller-net-1: R12.2, R13.1
heater_controller-net-2: R3.2, R4.1
heater_controller-net-3: R5.2, R12.1
heater_controller-net-4: R14.2, R15.1
heater_controller-net-5: R4.2, R5.1
heater_controller-net-6: R13.2, R14.1
hv: C8.1, R2.1, U7.1, U7.3
hv-2: C4.1, C9.1, R9.1, R11.1, U6.2, U7.5
hv-3: C5.1, C6.1, C7.1, U6.6

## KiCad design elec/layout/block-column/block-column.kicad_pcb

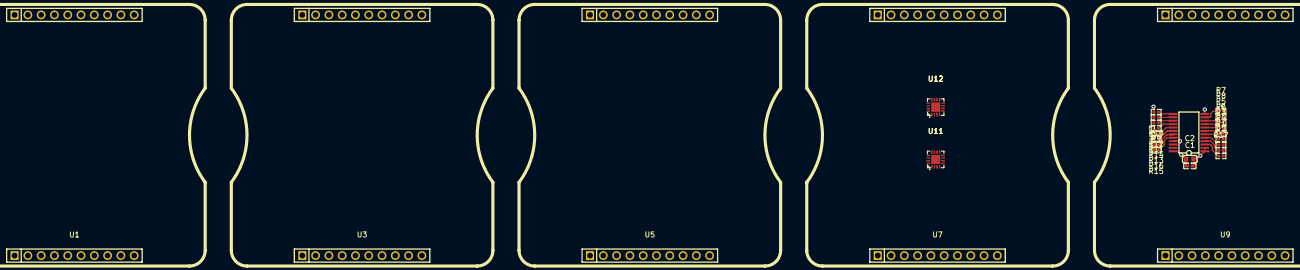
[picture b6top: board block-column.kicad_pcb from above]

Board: 2 copper layers, 32 parts (0 on the bottom side), 43 nets.

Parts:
C1: 100nF ±10% 16V X7R; C0402-b3ef17
C2: 2.2µF ±10% 16V X5R; C0603-bd72f6
R1, R2, R3, R4, R5, R6, R7, R8, R9, R10, R11, R12, R13, R14, R15, R16, R17: 10kΩ ±1% 62.5mW; R0402-56259e
U1, U2, U3, U4, U5, U6, U7, U8, U9, U10: HDR-TH_10P-P2.54-V-F-f96416
U11, U12: QFN-16_L3.0-W3.0-P0.50-BL-EP1.7-3a4c56
U13: TSSOP-24_L7.8-W4.4-P0.65-LS6.4-BL

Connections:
RESET: U11.1, U11.14, U11.15
RESET_: R17.1, U13.3
SC0: R1.1, U13.5
SC1: R3.1, U13.7
SC2: R5.1, U13.9
SC3: R7.1, U13.11
SC4: R9.1, U13.14
SC5: R11.1, U13.16
SC6: R13.1, U13.18
SC7: R15.1, U13.20
SD0: R2.1, U13.4
SD1: R4.1, U13.6
SD2: R6.1, U13.8
SD3: R8.1, U13.10
SD4: R10.1, U13.13
SD5: R12.1, U13.15
SD6: R14.1, U13.17
SD7: R16.1, U13.19
VCCP: U12.1, U12.14, U12.15
base_0-gnd: U1.1, U1.4, U1.7, U1.10, U2.1, U2.4, U2.7, U2.10
base_0-hv: U2.8, U2.9
base_0-hv-1: U2.2, U2.3
base_0-hv-2: U2.5, U2.6
base_1-gnd: U3.1, U3.4, U3.7, U3.10, U4.1, U4.4, U4.7, U4.10
base_1-hv: U4.2, U4.3
base_1-hv-1: U4.8, U4.9
base_1-hv-2: U4.5, U4.6
base_2-gnd: U5.1, U5.4, U5.7, U5.10, U6.1, U6.4, U6.7, U6.10
base_2-hv: U6.2, U6.3
base_2-hv-1: U6.5, U6.6
base_2-hv-2: U6.8, U6.9
base_3-gnd: U7.1, U7.4, U7.7, U7.10, U8.1, U8.4, U8.7, U8.10
base_3-hv: U8.2, U8.3
base_3-hv-1: U8.5, U8.6
base_3-hv-2: U8.8, U8.9
base_4-gnd: U9.1, U9.4, U9.7, U9.10, U10.1, U10.4, U10.7, U10.10
base_4-hv: U10.5, U10.6
base_4-hv-1: U10.2, U10.3
base_4-hv-2: U10.8, U10.9
gnd: C1.2, C2.2, U13.1, U13.2, U13.12, U13.21
gpio_expander_1-gnd: U11.6, U11.17
gpio_expander_2-gnd: U12.6, U12.17
hv: C1.1, C2.1, R1.2, R2.2, R3.2, R4.2, R5.2, R6.2, R7.2, R8.2, R9.2, R10.2, R11.2, R12.2, R13.2, R14.2, R15.2, R16.2, R17.2, U13.24
